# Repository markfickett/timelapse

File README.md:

# Outdoor Battery Powered dSLR Time Lapse

## Parts

This is based around a dSLR for the high-quality image sensor and lenses. A Nikon D90 costs around $200 used in 2015, and has connections for a wired remote and external power supply.

### Control board

The control board is Arduino-based, using a bare ATMega328p, with a MOSFET to control camera power and an opto-isolater to control camera exposure.

#### Components

Many of these parts may be found cheaper at Mouser or DigiKey, but SparkFun or Adafruit makes finding the right component and learning to use it easy.

 * ATMega328p [$6 from Sparkfun](https://www.sparkfun.com/products/10524) and 28-DIP socket [$1 from SparkFun](https://www.sparkfun.com/products/7942).
 * optoisolator (2+ channel) [$2 from Mouser](http://www.mouser.com/ProductDetail/Vishay-Semiconductors/ILD2/?qs=sGAEpiMZZMteimceiIVCBwfsK9X9U0O6VGEot9Q9ETk%3d)
 * Chrono Dot real time clock module [$20 from Adafruit](https://www.adafruit.com/products/255)
 * MOSFET [$1 from Sparkfun](https://www.sparkfun.com/products/10213) for camera power control
 * NPN transistor [$1 from Sparkfun](https://www.sparkfun.com/products/521) for LED display power control
 * photoresistor (CdS) [$1 from Adafruit](http://www.adafruit.com/product/161), to sense the camera's activity LED and ambient light levels
 * 5V 1A buck converter for regulated power [$15 from Adafruit](https://www.adafruit.com/product/1065). Idle current of under 2mA.
 * Small tactile switches [$5 for 20 from Adafruit](https://www.adafruit.com/product/1489) for a reset and debug buttons.
 * I2C 7-segment display [$20 from Adafruit](https://www.adafruit.com/product/878), though I might go for the [alphanumeric version](https://www.adafruit.com/product/1911) were I starting again.
 * assorted resistors
 * 22 uF electrolytic capacitor for filtering

I used [SparkFun's $20 Tiny AVR Programmer](https://www.sparkfun.com/products/11801) to [upload to the bare ATMega328](https://www.sparkfun.com/products/11801#comment-561f19cbce395f7a0d8b4567). I soldered [female headers](https://www.adafruit.com/product/598) on the programmer, and used Adafruit's [$4 female-female jumpers](https://www.adafruit.com/product/266) along with [extra-long headers](https://www.adafruit.com/product/400) to jump to the ISP header on the board.

#### Circuit

See the `eagle/` subdirectory for circuit and PCB details including [schematic PDF](eagle/timelapse.sch.pdf).

I designed PCBs using EAGLE's non-commercial free license and autolayout, following [SparkFun's tutorial](https://learn.sparkfun.com/tutorials/using-eagle-schematic), and had them printed by [OSH Park](https://oshpark.com/).

### Off-Board Parts and Connectors

 * 12v to 9v DC regulator [$8 on Amazon](http://www.amazon.com/gp/product/B00A71E52G) for power to camera (draws 12mA @ 12v with no load)
 * AC adapter plug (3D printed plug for Nikon D90; [photo](nikond90acplug/151021nikond90acplugendquarter.jpg), [STL file](nikond90acplug/NikonD90AcPlugReducedH.stl), [Thingiverse](https://www.thingiverse.com/thing:1107374/apps/print/))
 * XT60s (power connections, [$2 from Sparkfun](https://www.sparkfun.com/products/10474), compare at HobbyKing)
 * servo cables (peripheral/control connections)
 * lamp cord (battery connection)
 * wired dSLR remote [$6 MC-DC2 clone on Amazon](http://www.amazon.com/gp/product/B003JR8GCU)

### Hardware

A Pelican case provides a sturdy, watertight enclosure which is easy to open and close; and the fins on the hinge side facilitate mounting.

 * Pelican case 1300 NF ($60 on eBay)
 * glass (from a small thrift-store picture frame; attached with JB weld)
 * silica gel (dried and reused)
 * treated wood and screws for mounting
 * 5W solar panel ([$35 on Amazon](https://www.amazon.com/gp/product/B004FOEUI0)) for locations with a fair amount of direct sun, or as overkill, 30W panel ([$60 on Amazon](https://www.amazon.com/gp/product/B00JDRG69K))
 * SLA solar charge controller (this [$10 CMP12 on Amazon](https://www.amazon.com/gp/product/B010FNO9NU) works well, but draws 10mA when idle, even with its indicator LEDs clipped)
 * 12v sealed lead-acid battery (a 4Ah version for home security systems works well; [$20 on Amazon](https://www.amazon.com/dp/B00GYHBACA))

## Related

[Brinno](http://brinno.com/time-lapse-camera/TLC200Pro) makes a 1.3MP HDR timelapse camera with CS-mount lenses and a weatherproof case, claiming 45-day battery life on 4xAA.

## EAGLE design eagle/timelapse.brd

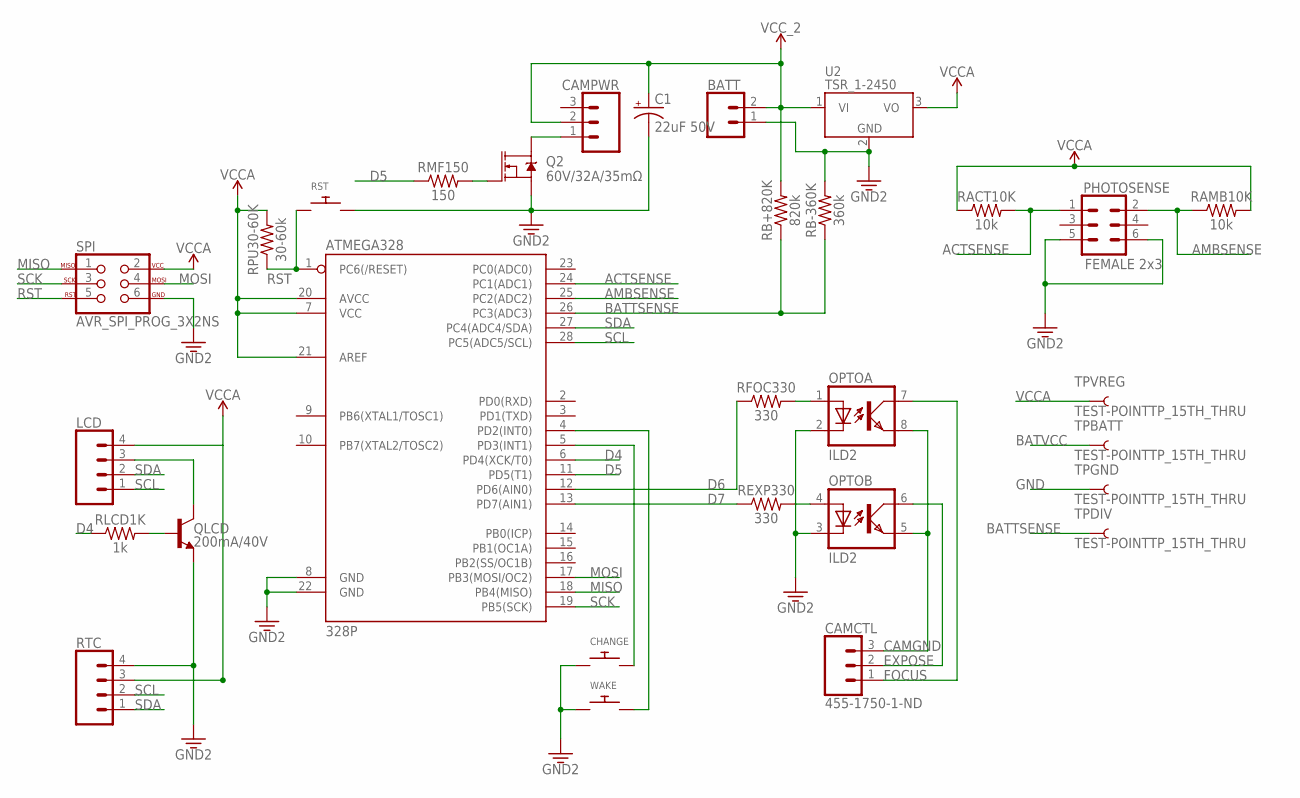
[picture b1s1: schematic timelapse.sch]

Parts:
ATMEGA328: 328P; DIP28
BATT: CONN_02; 1X02
C1: 22uF 50V; CPOL-RADIAL-2.5MM-5MM
CAMCTL: 455-1750-1-ND; 1X03
CAMPWR: CONN_03; 1X03
CHANGE: SWITCH_PUSHBUTTONEVQ-PE; TACT_PANA-EVQ
LCD: CONN_04; 1X04
OPTO: ILD2; DIL08
PHOTOSENSE: FEMALE 2x3; 2X3
Q2: 60V/32A/35mΩ; TO220V
QLCD: 200mA/40V; TO-92
RACT10K: 10k; AXIAL-0.3
RAMB10K: 10k; AXIAL-0.3
RB+820K: 820k; AXIAL-0.3
RB-360K: 360k; AXIAL-0.3
REXP330: 330; AXIAL-0.3
RFOC330: 330; AXIAL-0.3
RLCD1K: 1k; AXIAL-0.3
RMF150: 150; AXIAL-0.3
RPU30-60K: 30-60k; AXIAL-0.3
RST: SWITCH_PUSHBUTTONEVQ-PE; TACT_PANA-EVQ
RTC: CONN_04; 1X04
SPI: AVR_SPI_PROG_3X2NS; 2X3-NS
TPBATT: TEST-POINTTP_15TH_THRU; TP_15TH
TPDIV: TEST-POINTTP_15TH_THRU; TP_15TH
TPGND: TEST-POINTTP_15TH_THRU; TP_15TH
TPVREG: TEST-POINTTP_15TH_THRU; TP_15TH
U2: TSR_1-2450; TSR-1
WAKE: SWITCH_PUSHBUTTONEVQ-PE; TACT_PANA-EVQ

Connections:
ACTSENSE: ATMEGA328.24 (PC1(ADC1)), PHOTOSENSE.1, RACT10K.P$2 (2)
AMBSENSE: ATMEGA328.25 (PC2(ADC2)), PHOTOSENSE.2, RAMB10K.P$1 (1)
BATTSENSE: ATMEGA328.26 (PC3(ADC3)), RB+820K.P$1 (1), RB-360K.P$1 (1), TPDIV.P$1
BATVCC: BATT.2, C1.1 (+), CAMPWR.2, RB+820K.P$2 (2), TPBATT.P$1, U2.1 (VI)
CAMGND: CAMCTL.3, OPTO.5 (EMIT), OPTO.8 (EMIT)
D4: ATMEGA328.6 (PD4(XCK/T0)), RLCD1K.P$1 (1)
D5: ATMEGA328.11 (PD5(T1)), RMF150.P$1 (1)
D6: ATMEGA328.12 (PD6(AIN0)), RFOC330.P$1 (1)
D7: ATMEGA328.13 (PD7(AIN1)), REXP330.P$1 (1)
EXPOSE: CAMCTL.2, OPTO.6 (COL)
FOCUS: CAMCTL.1, OPTO.7 (COL)
GND: ATMEGA328.8 (GND), ATMEGA328.22 (GND), BATT.1, C1.2 (-), CHANGE.P$1, OPTO.2 (C), OPTO.3 (C), PHOTOSENSE.5, PHOTOSENSE.6, Q2.3 (S), QLCD.1 (E), RB-360K.P$2 (2), RST.P$2, RTC.4, SPI.6, TPGND.P$1, U2.2 (GND), WAKE.P$1
MISO: ATMEGA328.18 (PB4(MISO)), SPI.1
MOSI: ATMEGA328.17 (PB3(MOSI/OC2)), SPI.4
unnamed: OPTO.1 (A), RFOC330.P$2 (2)
unnamed: OPTO.4 (A), REXP330.P$2 (2)
unnamed: QLCD.2 (B), RLCD1K.P$2 (2)
unnamed: LCD.3, QLCD.3 (C)
unnamed: Q2.1 (G), RMF150.P$2 (2)
unnamed: ATMEGA328.5 (PD3(INT1)), CHANGE.P$2
unnamed: ATMEGA328.4 (PD2(INT0)), WAKE.P$2
unnamed: CAMPWR.1, Q2.2 (D)
RST: ATMEGA328.1 (PC6(/RESET)), RPU30-60K.P$1 (1), RST.P$1, SPI.5
SCK: ATMEGA328.19 (PB5(SCK)), SPI.3
SCL: ATMEGA328.28 (PC5(ADC5/SCL)), LCD.1, RTC.2
SDA: ATMEGA328.27 (PC4(ADC4/SDA)), LCD.2, RTC.1
VCCA: ATMEGA328.7 (VCC), ATMEGA328.20 (AVCC), ATMEGA328.21 (AREF), LCD.4, RACT10K.P$1 (1), RAMB10K.P$2 (2), RPU30-60K.P$2 (2), RTC.3, SPI.2, TPVREG.P$1, U2.3 (VO)

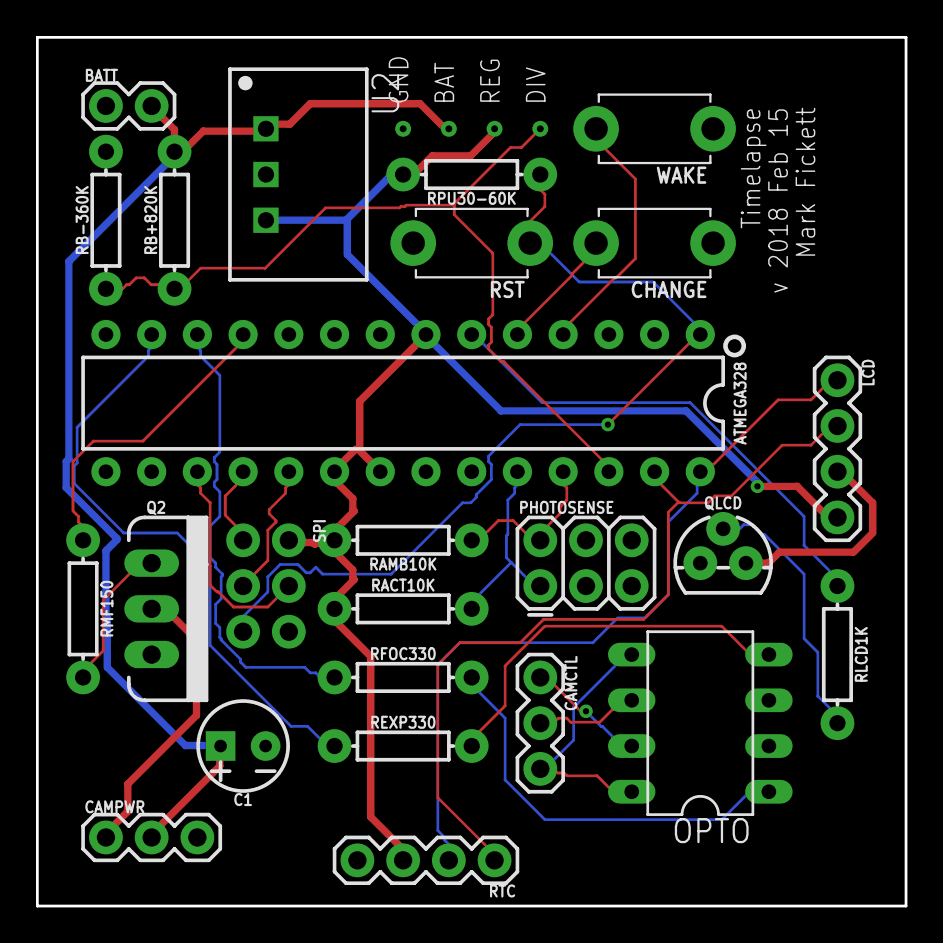
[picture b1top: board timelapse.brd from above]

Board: 2 copper layers, 48.3 x 48.3 mm, 29 parts (0 on the bottom side), 27 nets.

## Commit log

2015-04-26 Read temperature and humidity and log to serial.
2015-04-26 Read RTC time and operate camera.
2015-04-27 Log unregulated supply voltage.
2015-04-27 Condense log line format.
2015-04-27 Write log data to SD card.
2015-04-29 Fix typo in battery voltage computation comment.
2015-04-29 Add script for combining/formatting logs, graph using js dygraphs.
2015-05-02 Add second voltage input, pull out voltage printer helper function.
2015-05-02 Add current-drawn note for DHT22.
2015-05-02 Add note on uSD card current draw.
2015-05-03 Switch to keep the target photo time on a regular interval. Add low-power sleep using Narcoleptic.
2015-05-05 Fix extra newline in csv.
2015-05-05 Add script to fix logs created with newline bug (fixed in previous commit).
2015-05-05 Remove fixnewline script.
2015-05-05 Update logs combiner with new voltage divider values, status printing; update graph to use subdir.
2015-05-06 Add note about SanDisk 4GB card current.
2015-05-06 Add more power notes. Add comment about using Narcoleptic.millis() in DHT22.
2015-05-06 Add power usage log and graph with annotations.
2015-05-06 Annotate unknown power usage point, adjust descriptions.
2015-05-06 Add dygraph credit and instructions on graph.
2015-05-06 Add analysis to graph.
2015-05-06 Add script to sum power usage.
2015-08-19 Add note for hovering over markers on power graph.
2015-08-19 Rearrange pins, use AREF, adjust timing for testing.
2015-08-19 Combine-logs script: update AREF, check for __main__, improve error reporting, take LOGS_DIR from args.
2015-08-20 Adjust voltage divider constants.
2015-08-25 Make the switch to keep the camera on a toggle. Add switching between slow and fast picture-taking rates.
2015-08-25 Fill in current usage while taking a photo in the overview doc.
2015-08-25 Re-expand labels in data printing.
2015-08-25 Print message when done waiting.
2015-08-25 Revert fast-mode duration to omit arithematic.
2015-08-30 Switch to PIN_DHT22 for conformity.
2015-08-30 Add status LED with signaling for short / fast modes. Remove frequent debug printing of next scheduled time.
2015-08-30 Add a sensor for the camera memory-access LED, and wait for power-on and photo-write instead of hardcoding timings.
2015-08-30 Shorten duration waiting while camera is on.
2015-09-29 Fast mode interval: 10 minutes.
2015-09-29 Switch fast mode versus schedule mode to a #define. Doc dependency sources.
2015-09-29 Split defines out into config.h.
2015-09-29 Only take fast-mode photos when it is light.
2016-06-30 Fix up incorrectly recorded negative temperatures from DHT22 library in combinelogs.
2016-07-27 Do not halt for SD card error.
2016-07-27 Schedule fast-mode photos on round 10-minute marks. Only take fast-mode photos when PV and battery voltage are sufficiently high.
2016-07-27 Increase log interval to 30s.
2016-07-27 Add logging for photo decision.
2016-07-28 Turn off reading PV voltage.
2016-07-28 Disable fast-mode photos at night.
2016-07-30 Add note on battery voltage threshold.
2018-02-04 Add README for first version hardware with Arduino Pro.
2018-02-04 Add gitignore.
2018-02-04 Remove voltage / temperature logs.
2018-02-10 Add skeleton of using 7 segment LED and LowPower, initializing new pins.
2018-02-11 Add debug output, conditions except schdedule.
2018-02-11 Fix Vcc: floats in divider arithematic, print analog reading, adjust actual AREF, restructure equation for clarity.
2018-02-11 Add eagle subdirectory with schema and board layout.
2018-02-11 Remove old EAGLE files, fix missing wires in schema and add test points.
2018-02-11 Split button-press handling into separate file.
2018-02-13 Implement scheduling, and debug info for same.
2018-02-13 Sense camera activity, run power/shutter.
2018-02-14 Add camera power on/off debug item.
2018-02-14 fix clock initialization
2018-02-14 clear presses on debug exit
2018-02-14 Save/restore photo period in EEPROM.
2018-02-14 rm obselete Serial, add delay for initial 7seg startup.
2018-02-15 Add correcting factor to voltage divide for vcc.
2018-02-15 Add capacitor for camera power supply.
2018-02-28 Store lastPhotoTime in EEPROM.
2018-03-02 update description in README
2018-03-03 Add SketchUp and STL files for Nikon AC plug.
2018-03-03 Remove extra Nikon AC plug files.
2018-03-03 Add Nikon AC plug to README.
2018-03-31 no-load current note for 9v regulator
2018-04-02 Add CAMERA_POWER_ALWAYS_ON macro to work around camera internal battery depleting / settings resetting.
2018-04-22 Add link to Brinno.
2018-08-14 Add script to flatten camera-output directories.
2018-08-14 flatten script fixes
2018-08-14 rm version from flattendirs shebang
2019-03-07 Switch flattendirs script to python3 explicitly.
2019-03-07 EAGLE project file update.

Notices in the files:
parts and their libraries:
SparkFun-IC-Microcontroller: Licensing: Creative Commons ShareAlike 4.0 International - https://creativecommons.org/licenses/by-sa/4.0
